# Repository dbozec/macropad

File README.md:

# Macropad

This is a custom macropad with 4x4 keys and a rotary knob.

I wanted it to be wireless so it is built arround an ESP32 module with Bluetooth.

It is built to be used with Kailh Choc keyswitches to have a lower profile than classical mechanical switches.

Shortly after I started to work on this project, the folks from [DeepSea-Developments](https://github.com/DeepSea-Developments) announced their own work on the [DeepDeck](https://deepdeck.co/) macropad. So I benefit from their work to design my own macropad.

I also switched from other existing firmwares I was trying to their work on the [DeepDeck firmware](https://github.com/DeepSea-Developments/DeepDeck.Ahuyama.fw)

## Warnings
My work is distributed in the home it can be useful, but **WITHOUT ANY WARRANTY**

This product is meant to be used with battery, but v1.0 has never be tested in battery power mode right now, so take care of what you do.

## Thanks
- To [DeepSea-Developments](https://www.deepseadev.com/), creators of the [DeepDeck](https://deepdeck.co/) macropad for their work.
- To [Yannick Hemery](https://github.com/yhemery), for taking time to fine tune the DeepDeck firmware to fit my hardware design.

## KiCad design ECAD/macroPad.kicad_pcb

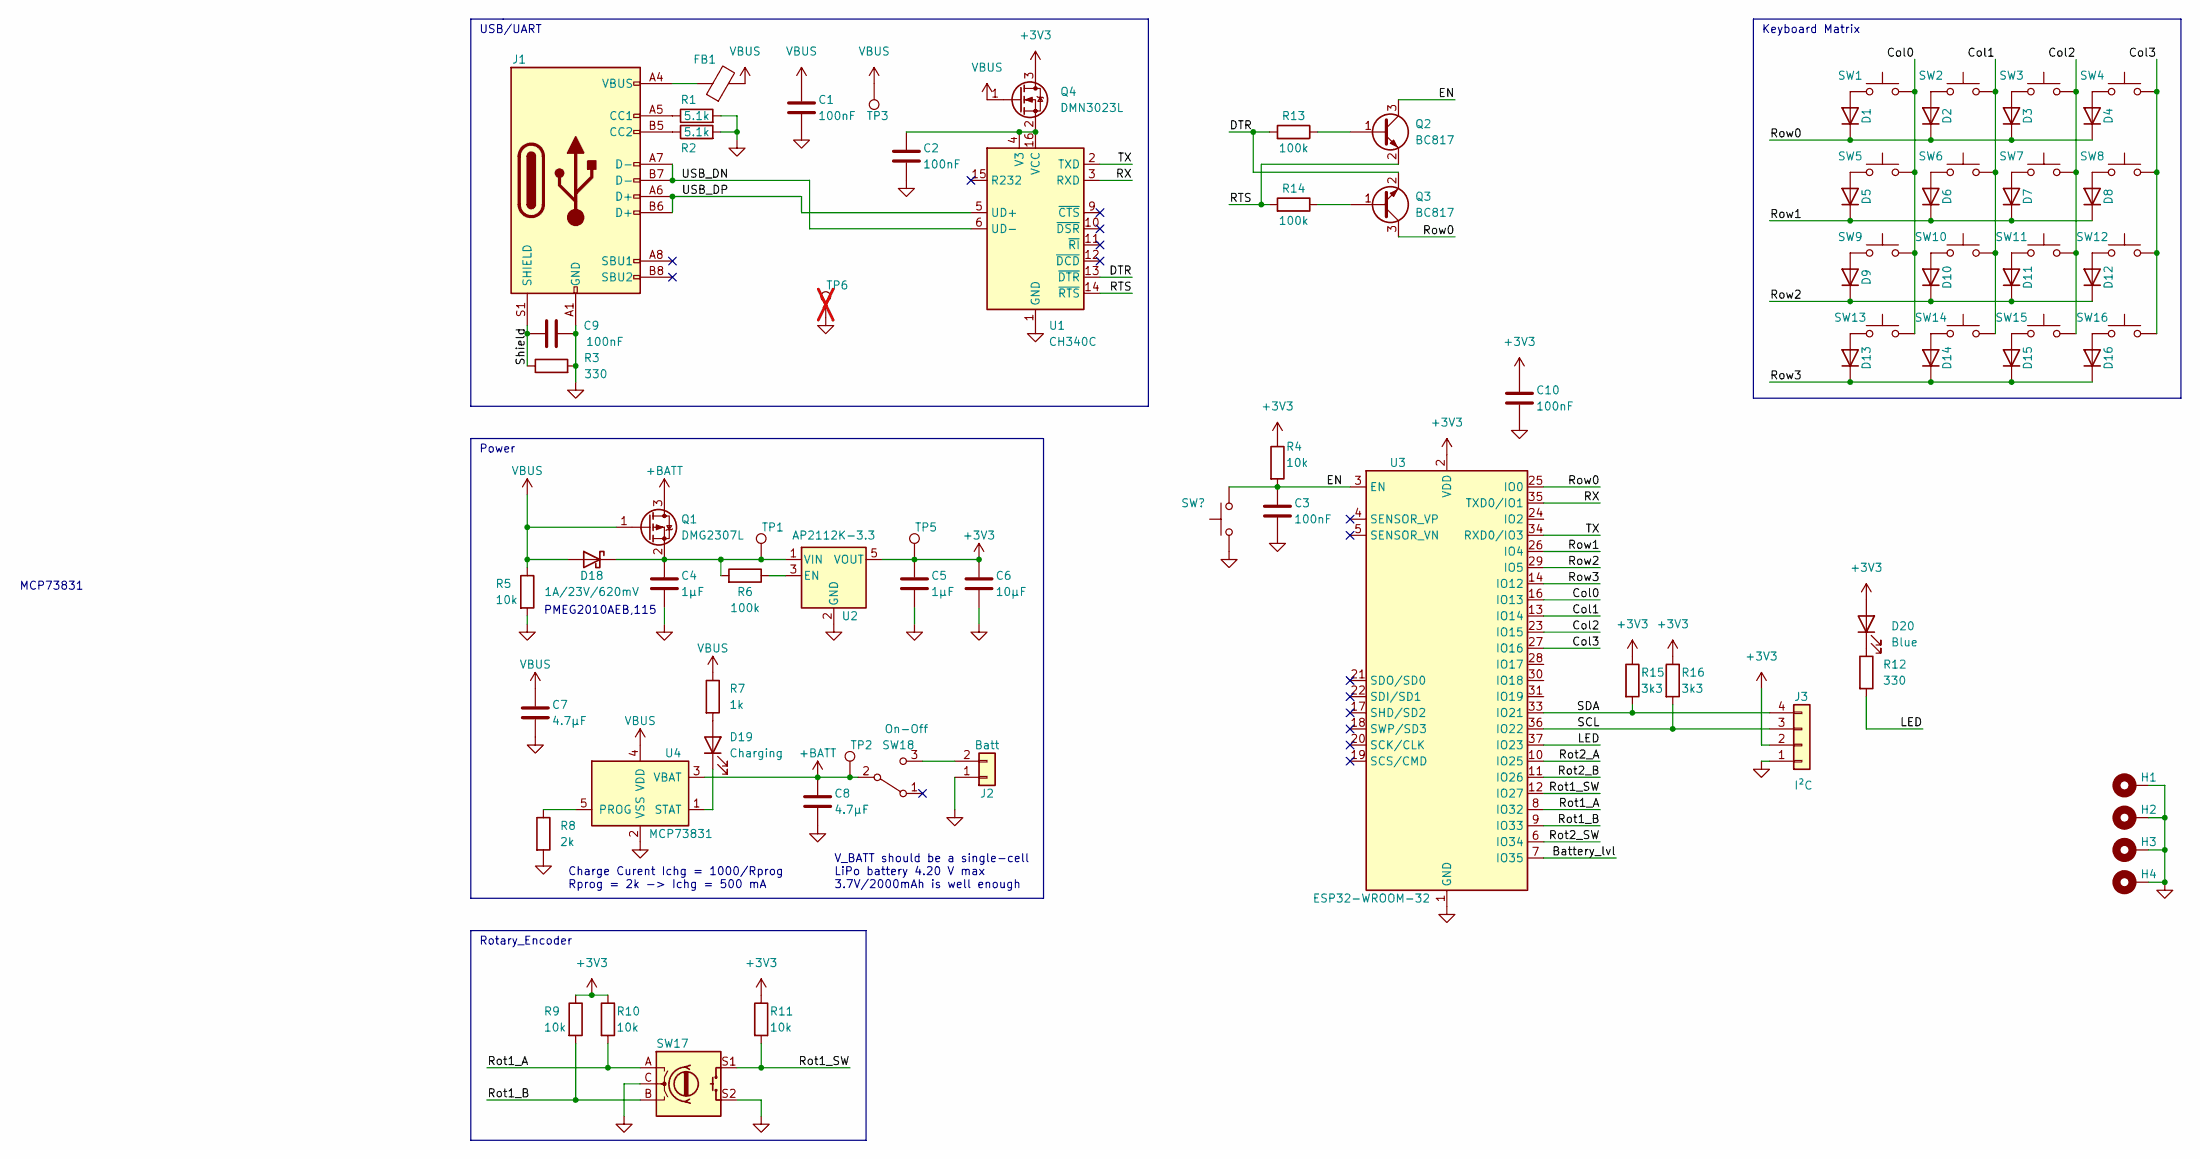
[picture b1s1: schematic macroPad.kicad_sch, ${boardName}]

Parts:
C1, C2, C3, C9, C10: 100nF; C_0603_1608Metric_Pad1.08x0.95mm_HandSolder
C4, C5: 1µF; C_0603_1608Metric_Pad1.08x0.95mm_HandSolder
C6: 10µF; C_0805_2012Metric_Pad1.18x1.45mm_HandSolder
C7, C8: 4.7µF; C_0805_2012Metric_Pad1.18x1.45mm_HandSolder
D1, D2, D3, D4, D5, D6, D7, D8, D9, D10, D11, D12, D13, D14, D15, D16: MMSD4148; D_SOD-123
D18: 1A/23V/620mV; D_SOD-523
D19: Charging; LED_0603_1608Metric_Pad1.05x0.95mm_HandSolder
D20: Blue; LED_0603_1608Metric_Pad1.05x0.95mm_HandSolder
FB1: FerriteBead; L_0805_2012Metric_Pad1.05x1.20mm_HandSolder
H1, H2, H3, H4: MountingHole_Pad; MountingHole_3.2mm_M3_Pad_Via
J1: USB_C_Receptacle_USB2.0; USB_C_Receptacle_HRO_TYPE-C-31-M-12
J2: Batt; JST_EH_S2B-EH_1x02_P2.50mm_Horizontal
J3: I²C; PinSocket_1x04_P2.54mm_Vertical
Q1: DMG2307L; SOT-23
Q2, Q3: BC817; SOT-23
Q4: DMN3023L
R1, R2: 5.1k; R_0603_1608Metric_Pad0.98x0.95mm_HandSolder
R3, R12: 330; R_0603_1608Metric_Pad0.98x0.95mm_HandSolder
R4, R5, R9, R10, R11: 10k; R_0603_1608Metric_Pad0.98x0.95mm_HandSolder
R6, R13, R14: 100k; R_0603_1608Metric_Pad0.98x0.95mm_HandSolder
R7: 1k; R_0603_1608Metric_Pad0.98x0.95mm_HandSolder
R8: 2k; R_0603_1608Metric_Pad0.98x0.95mm_HandSolder
R15, R16: 3k3; R_0603_1608Metric_Pad0.98x0.95mm_HandSolder
SW1, SW2, SW3, SW4, SW5, SW6, SW7, SW8, SW9, SW10, SW11, SW12, SW13, SW14, SW15, SW16: Keyswitch; PG1350_optional-socket
SW17: RotaryEncoder_Switch; RotaryEncoder_Bourns_PEC11S-929K-Switch_Vertical
SW18: On-Off; SW_Slide_Mini_Wurth_450404015514
TP1: Vin; TestPoint_Pad_D1.0mm
TP2: VBAT; TestPoint_Pad_D1.0mm
TP3: VBUS; TestPoint_Pad_D1.0mm
TP5: +3V3; TestPoint_Pad_D1.0mm
TP6: GND; TestPoint_Loop_D1.80mm_Drill1.0mm_Beaded; not fitted
U1: CH340C; SOIC-16_3.9x9.9mm_P1.27mm
U2: AP2112K-3.3; SOT-23-5
U3: ESP32-WROOM-32
U4: MCP73831; SOT-23-5

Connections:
+3V3: C5.1, C6.1, C10.1, D20.2 (A), J3.2, Q4.3 (D), R4.1, R9.1, R10.1, R11.1, R15.1, R16.1, TP5.1, U2.5 (VOUT), U3.2 (VDD)
+BATT: C8.1, Q1.3 (D), SW18.2 (B), TP2.1, U4.3 (VBAT)
/Battery_lvl: U3.7 (IO35)
/Col1: SW2.2, SW6.2, SW10.2, SW14.2, U3.13 (IO14)
/Col2: SW3.2, SW7.2, SW11.2, SW15.2, U3.23 (IO15)
/Col3: SW4.2, SW8.2, SW12.2, SW16.2, U3.27 (IO16)
/DTR: Q3.2 (E), R13.2, U1.13 (~DTR)
/LED: R12.2, U3.37 (IO23)
/RTS: Q2.2 (E), R14.2, U1.14 (~RTS)
/RX: U1.3 (RXD), U3.35 (TXD0/IO1)
/Rot1_A: R10.2, SW17.A, U3.8 (IO32)
/Rot1_B: R9.2, SW17.B, U3.9 (IO33)
/Rot1_SW: R11.2, SW17.S1, U3.12 (IO27)
/Rot2_A: U3.10 (IO25)
/Rot2_B: U3.11 (IO26)
/Rot2_SW: U3.6 (IO34)
/Row0: D1.1 (K), D2.1 (K), D3.1 (K), D4.1 (K), Q3.3 (C), U3.25 (IO0)
/Row1: D5.1 (K), D6.1 (K), D7.1 (K), D8.1 (K), U3.26 (IO4)
/Row2: D9.1 (K), D10.1 (K), D11.1 (K), D12.1 (K), U3.29 (IO5)
/Row3: D13.1 (K), D14.1 (K), D15.1 (K), D16.1 (K), U3.14 (IO12)
/SCL: J3.3, R16.2, U3.36 (IO22)
/SDA: J3.4, R15.2, U3.33 (IO21)
/Shield: C9.1, J1.S1 (SHIELD), R3.1; also elsewhere on the board
/TX: U1.2 (TXD), U3.34 (RXD0/IO3)
/USB_DN: J1.A7 (D-), J1.B7 (D-), U1.6 (UD-); also elsewhere on the board
/USB_DP: J1.A6 (D+), J1.B6 (D+), U1.5 (UD+); also elsewhere on the board
unnamed: C2.1, Q4.2 (S), U1.4 (V3), U1.16 (VCC)
unnamed: C4.1, D18.1 (K), Q1.2 (S), R6.2, TP1.1, U2.1 (VIN)
unnamed: D2.2 (A), SW2.1
unnamed: D3.2 (A), SW3.1
unnamed: D4.2 (A), SW4.1
unnamed: D5.2 (A), SW5.1
unnamed: D6.2 (A), SW6.1
unnamed: D7.2 (A), SW7.1
unnamed: D8.2 (A), SW8.1
unnamed: D9.2 (A), SW9.1
unnamed: D10.2 (A), SW10.1
unnamed: D11.2 (A), SW11.1
unnamed: D12.2 (A), SW12.1
unnamed: D13.2 (A), SW13.1
unnamed: D14.2 (A), SW14.1
unnamed: D15.2 (A), SW15.1
unnamed: D16.2 (A), SW16.1
unnamed: D19.1 (K), U4.1 (STAT)
unnamed: D19.2 (A), R7.2
unnamed: D20.1 (K), R12.1
unnamed 46: FB1.1, J1.A4 (VBUS), J1.A9 (VBUS), J1.B4 (VBUS), J1.B9 (VBUS); also elsewhere on the board
unnamed 47: J1.A5 (CC1), R1.1; also elsewhere on the board
unnamed 48: J1.B5 (CC2), R2.1; also elsewhere on the board
unnamed: Q2.1 (B), R13.1
unnamed: Q3.1 (B), R14.1
unnamed: R6.1, U2.3 (EN)
unnamed: R8.1, U4.5 (PROG)
unnamed: J2.2, SW18.3 (C)
VBUS: C1.1, C7.1, D18.2 (A), FB1.2, Q1.1 (G), Q4.1 (G), R5.1, R7.1, TP3.1, U4.4 (VDD)

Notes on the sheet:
USB/UART
Power
MCP73831
V_BATT should be a single-cell LiPo battery 4.20 V max 3.7V/2000mAh is well enough
PMEG2010AEB,115
Rotary_Encoder
Keyboard Matrix
Charge Curent Ichg = 1000/Rprog Rprog = 2k -> Ichg = 500 mA

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
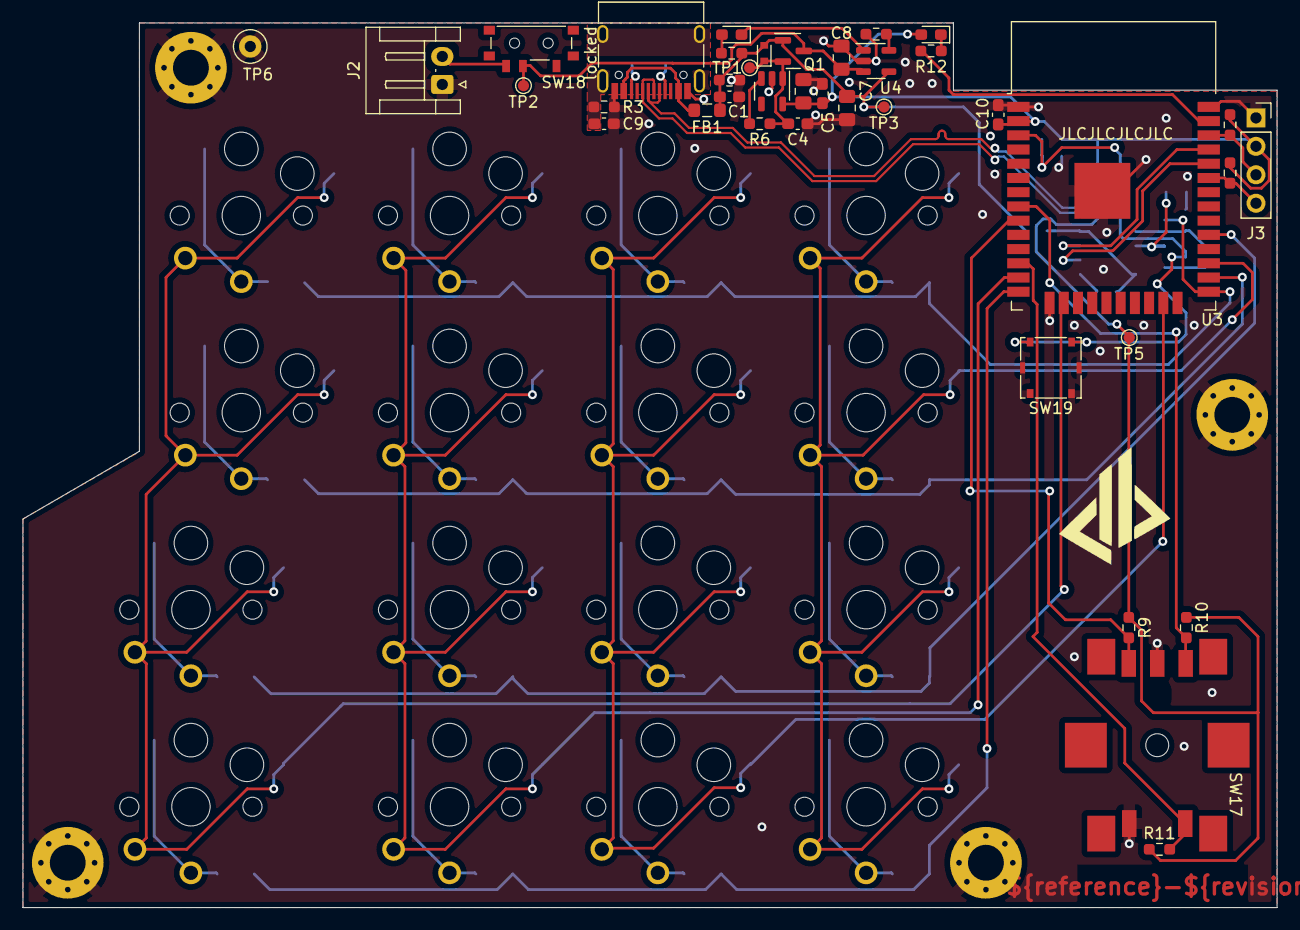
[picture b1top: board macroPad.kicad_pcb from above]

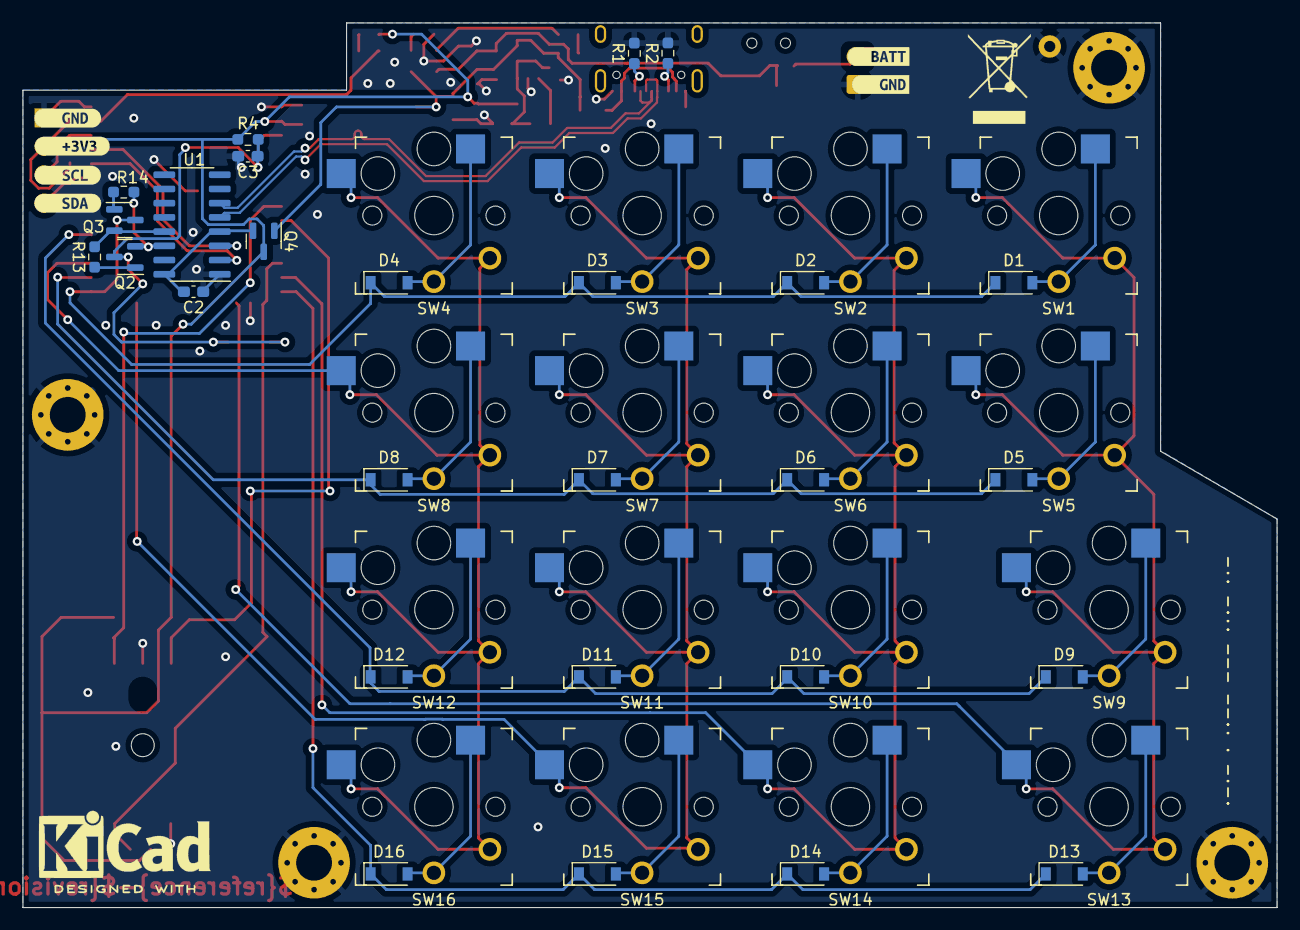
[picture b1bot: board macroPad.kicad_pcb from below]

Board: 2 copper layers, 112.0 x 79.0 mm, 91 parts (33 on the bottom side), 55 nets.

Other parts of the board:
SW19: Reset; SW_Tact_5x5mm_Wurth_431183015816
kibuzzard-63541E8A: G***; kibuzzard-63541E8A
kibuzzard-635127E0: G***; kibuzzard-635127E0
kibuzzard-6351268B: G***; kibuzzard-6351268B
kibuzzard-63512619: G***; kibuzzard-63512619
kibuzzard-63512654: G***; kibuzzard-63512654
kibuzzard-63512665: G***; kibuzzard-63512665
locked: USB_C_Receptacle_USB2.0; USB_C_Receptacle_HRO_TYPE-C-31-M-12

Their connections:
/Shield: locked.S1 (SHIELD); also elsewhere on the board
/USB_DN: locked.A7 (D-), locked.B7 (D-); also elsewhere on the board
/USB_DP: locked.A6 (D+), locked.B6 (D+); also elsewhere on the board
unnamed 46: locked.A4 (VBUS), locked.A9 (VBUS), locked.B4 (VBUS), locked.B9 (VBUS); also elsewhere on the board
unnamed 47: locked.A5 (CC1); also elsewhere on the board
unnamed 48: locked.B5 (CC2); also elsewhere on the board

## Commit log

2023-10-26 initial commit, first prototype
2023-10-26 add missing image
2023-10-26 add gitignore
2023-10-26 fix README
